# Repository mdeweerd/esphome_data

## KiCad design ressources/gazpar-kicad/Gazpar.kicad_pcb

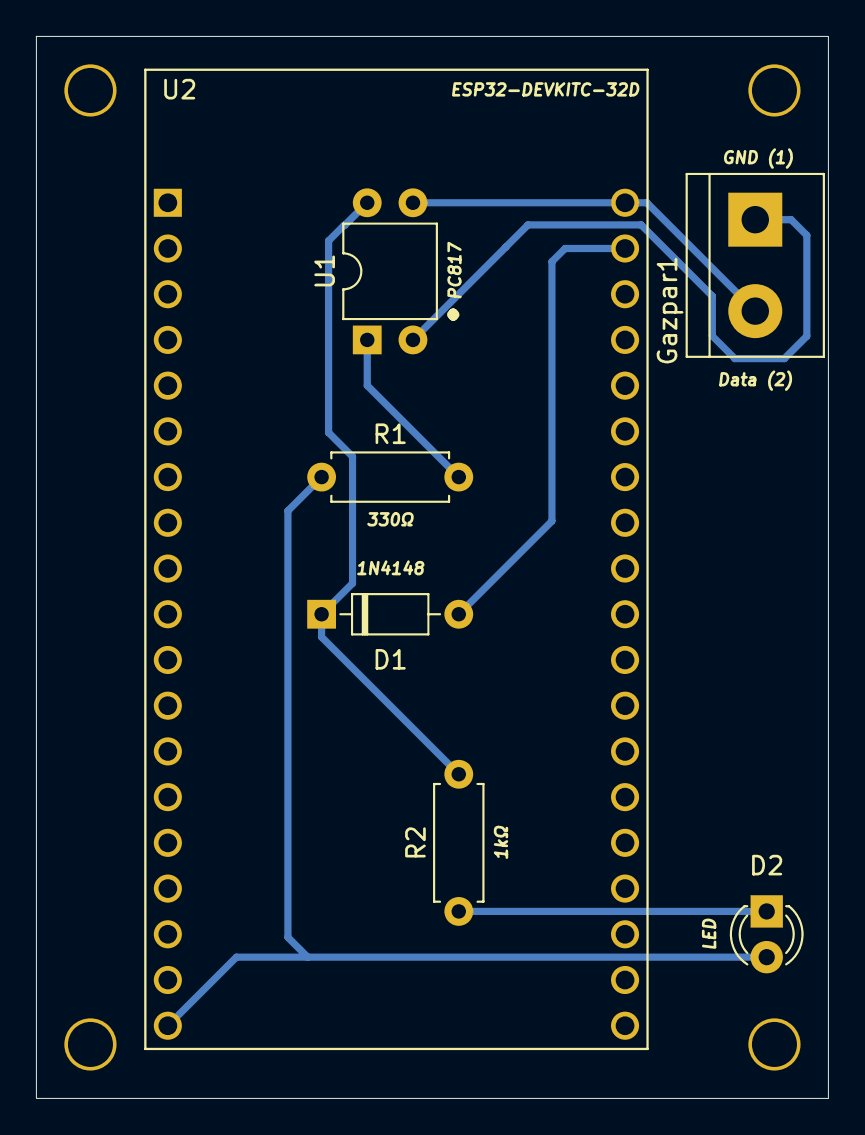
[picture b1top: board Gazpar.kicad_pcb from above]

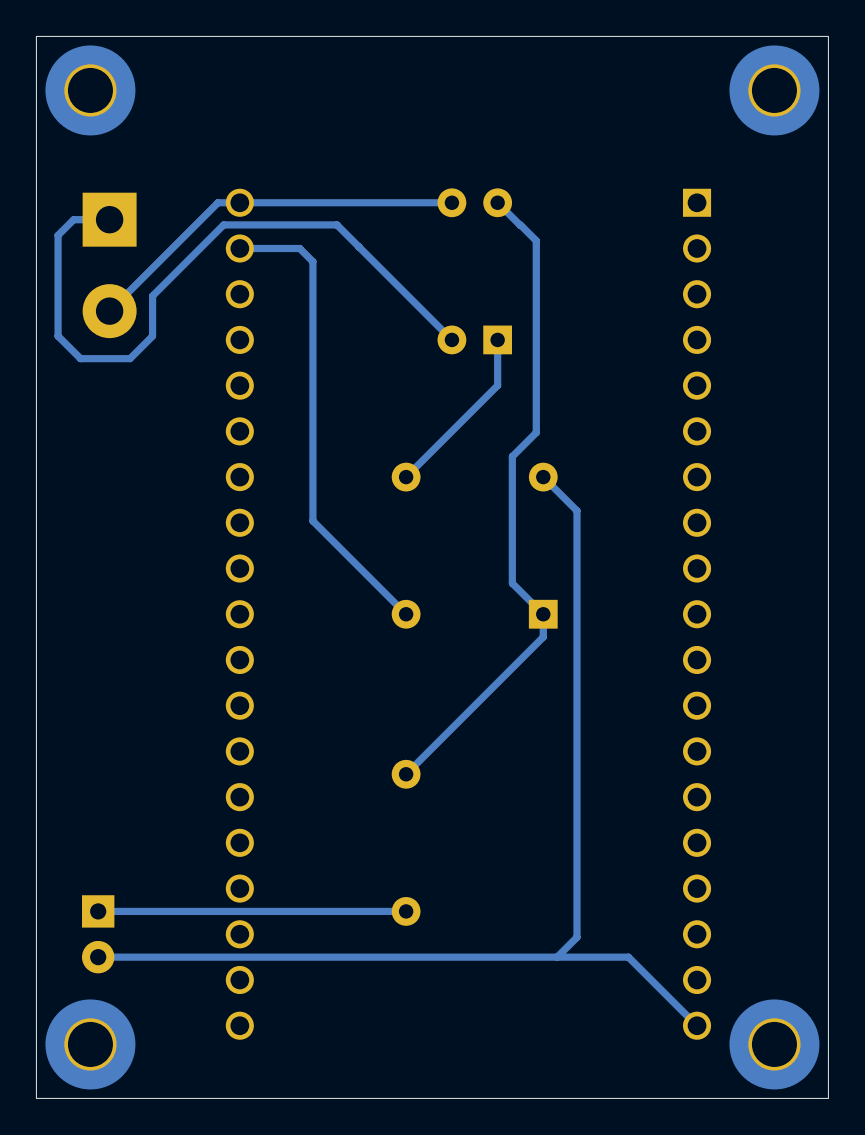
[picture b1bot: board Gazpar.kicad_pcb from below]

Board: 2 copper layers, 44.0 x 59.0 mm, 11 parts (4 on the bottom side), 7 nets.

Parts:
D1: 1N4148; D_DO-35_SOD27_P7.62mm_Horizontal
D2: LED; LED_D3.0mm
Gazpar1: G-; TerminalBlock_bornier-2_P5.08mm
H1, H2, H3, H4: MountingHole_2.5mm_Pad_TopOnly
R1: 330Ω; R_Axial_DIN0207_L6.3mm_D2.5mm_P7.62mm_Horizontal
R2: 1kΩ; R_Axial_DIN0207_L6.3mm_D2.5mm_P7.62mm_Horizontal
U1: PC817; DIP-4_W7.62mm
U2: ESP32-DEVKITC-32D; MODULE_ESP32-DEVKITC-32D

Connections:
unnamed: D1.1 (K), R2.2, U1.4
unnamed: D1.2 (A), U2.21 (IO23)
unnamed: D2.1 (K), R2.1
unnamed: D2.2 (A), R1.1, U2.19 (EXT_5V)
unnamed: Gazpar1.1, U1.2
unnamed: Gazpar1.2, U1.3, U2.20 (GND3)
unnamed: R1.2, U1.1

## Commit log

2023-02-14 Monocouche, fichiers de production, kibot, nomenclature, ...
2023-02-14 Add priced kicost
